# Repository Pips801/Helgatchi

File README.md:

this is an awesome project by 801labs.  calling it "by-sysaaron" was kind of stupid, sorry; i've been hacking around on it with ai.  at this time, i've added:
- a menu that lets you display any of Helga's animations
- a menu that lets you change the LED mode
- a menu that lets you trigger party mode
- a "continuous vibes" mode (NOTE: only use with flared base antenna)

# Helgatchi
Handheld BLE + WiFi Hunter

## What is it?
A portable, hand-held BLE beacon and WiFi AP scanner/hunter, with built-in alerting, 1.69” full-color screen, and external SMA-RP antenna all powered by the XIAO ESP32-S3. 

The Helgatchi will passively scan for BLE devices and WiFi SSIDs/APs, and alert when specific Manufacturers, naming schemes, or services are discovered. 

It can be configured to alert anything you want, such as:
- ALPR/Surveilance equipment
- Tactical equipment
- Cameras
- Hidden cameras
- Fitness wearables
- Audio/Video devices

You can create rules based on the following fields
|   🐑  	| MAC address 	| OUI (explicit) 	| OUI organization 	| MFG (explicit) 	| MFG organization 	| 802.11 SIG 	| Device name 	| SSID 	|
|------	|-------------	|----------------	|------------------	|----------------	|------------------	|------------	|-------------	|------	|
| WiFi 	|      ✅      	|        ✅       	|         ✅        	|        ❌       	|         ❌        	|      ✅     	|      ❌      	|   ✅  	|
| BLE  	|      ✅      	|        ✅       	|         ✅        	|        ✅       	|         ✅        	|      ❌     	|      ✅      	|   ❌  	|

## Key Features
- Enclosed, portable, battery powered handheld rechargeable BLE and WiFi scanner and hunter that can live in your pocket.
- Passively scans for beacons in the background in-between sleeping - maximizing battery life. You can configure 
- Powered by the XIAO ESP32-S3
- 6 RGB LEDs
- 1.69" rounded screen
- Vibration motor for alerts
- You can change
  - Color scheme
  - Alert settings
    - Vibrate
    - LEDs
    - Screen Wake
  - Scan settings
    - Sleep duration
    - Scan duration
  - Rules for alerts
    - MAC address (BLE, WiFi)
    - Manufacturer (BLE, WiFi OUI)
    - Device name (BLE name, WiFi SSID)
    - Service (BLE)

## Specifications

| Spec      | Info                                             	|
|----------	|---------------------------------------------------	|
| MCU      	| XIAO ESP32-S3                                     	|
| Flash    	| 8MB                                               	|
| Battery  	| 400mAh - 1200mAh 3.7v LiPo                        	|
| Screen   	| Waveshare 1.69” LCD - 240p × 280p                 	|
| Antenna  	| XIAO -> u.FL > back PCB > SMA-RP > 2.4Ghz antenna 	|
| Size     	| Width: 50mm Length: 80mm              	|

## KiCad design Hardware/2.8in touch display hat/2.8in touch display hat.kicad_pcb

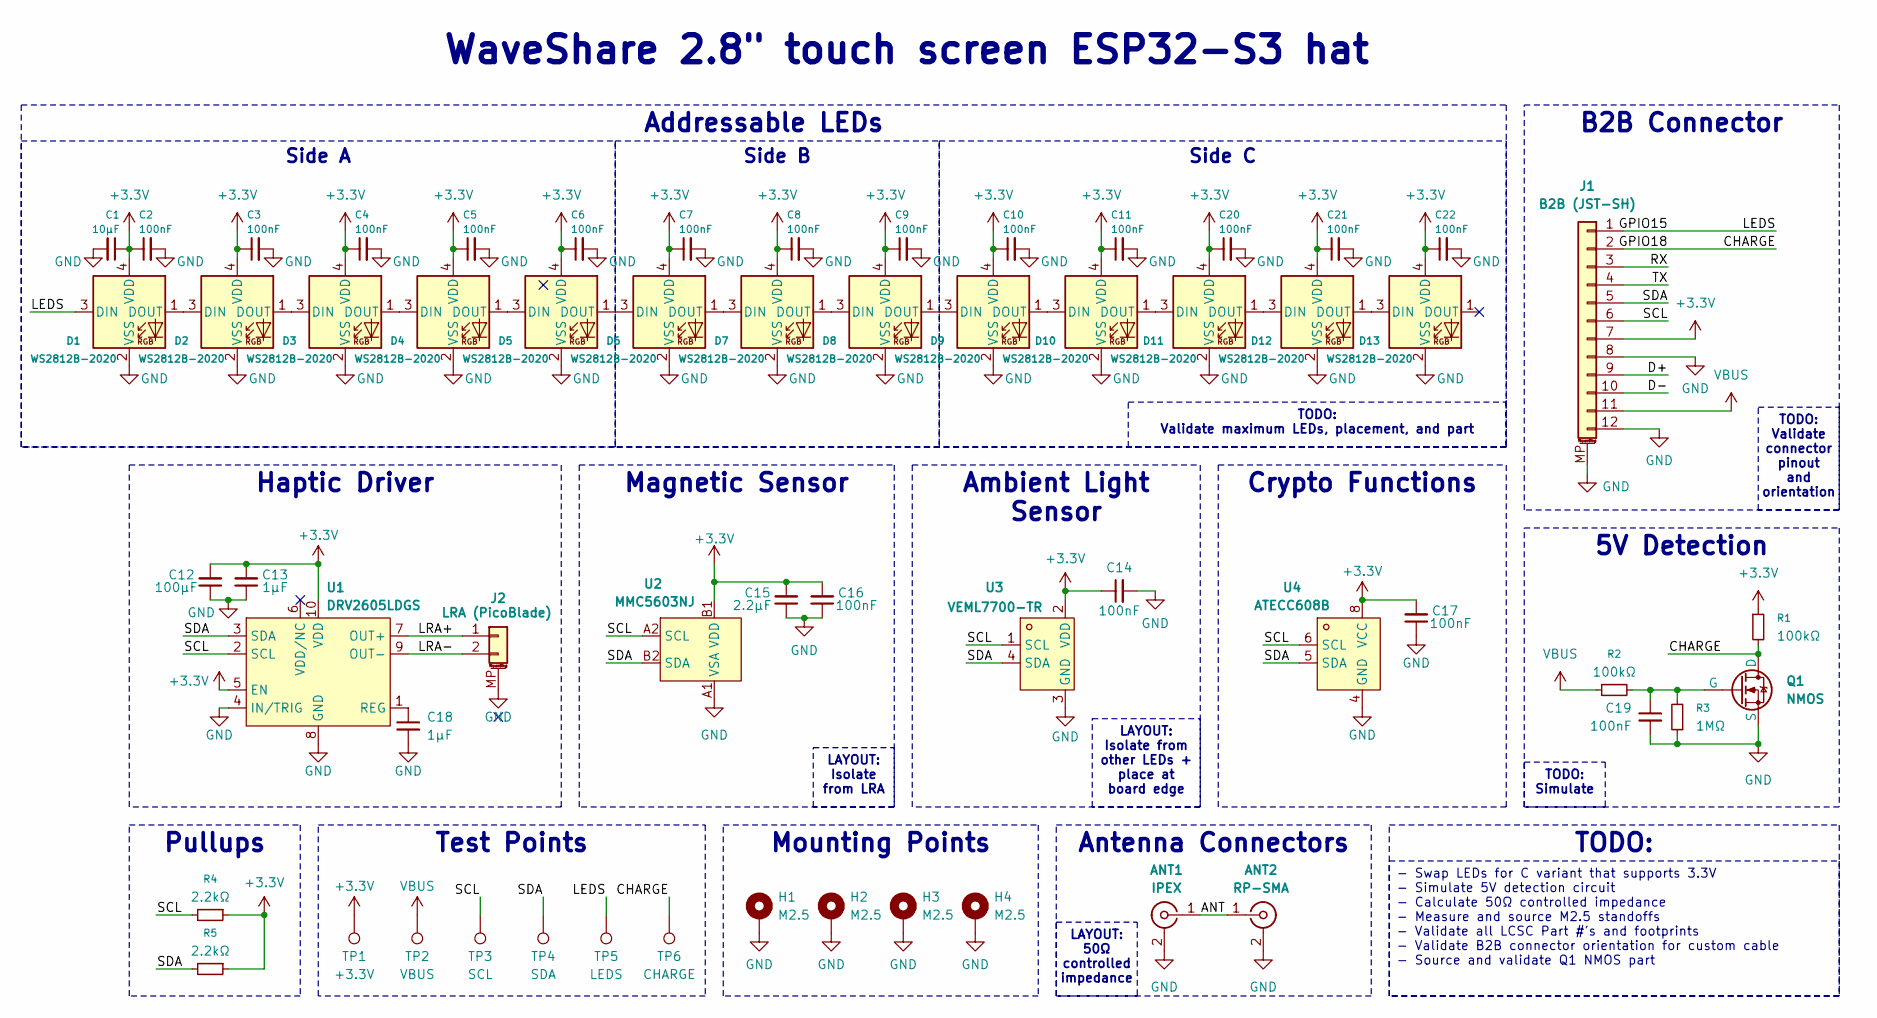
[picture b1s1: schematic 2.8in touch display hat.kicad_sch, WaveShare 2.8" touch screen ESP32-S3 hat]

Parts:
ANT1: IPEX; U.FL_Molex_MCRF_73412-0110_Vertical
ANT2: RP-SMA; SMA_Amphenol_901-143_Horizontal
C1: 10μF; C_1206_3216Metric
C2, C3, C4, C5, C6, C7, C8, C9, C10, C11, C14, C16, C17, C19, C20, C21, C22: 100nF; C_0603_1608Metric
C12: 100μF; C_0603_1608Metric
C13, C18: 1μF; C_0603_1608Metric
C15: 2.2μF; C_0603_1608Metric
D1, D2, D3, D4, D5, D6, D7, D8, D9, D10, D11, D12, D13: WS2812B-2020; LED_WS2812B-2020_PLCC4_2.0x2.0mm
H1, H2, H3, H4: M2.5; Mounting_Wuerth_WA-SMSI-M2.5_H1.5mm_9774015151
J1: B2B (JST-SH); JST_SH_SM12B-SRSS-TB_1x12-1MP_P1.00mm_Horizontal
J2: LRA (PicoBlade); Molex_PicoBlade_53261-0271_1x02-1MP_P1.25mm_Horizontal
Q1: NMOS; SOT-23-3
R1, R2: 100kΩ; R_0603_1608Metric
R3: 1MΩ; R_0603_1608Metric
R4, R5: 2.2kΩ; R_0603_1608Metric
TP1: +3.3V; TestPoint_Pad_D1.0mm
TP2: VBUS; TestPoint_Pad_D1.0mm
TP3: SCL; TestPoint_Pad_D1.0mm
TP4: SDA; TestPoint_Pad_D1.0mm
TP5: LEDS; TestPoint_Pad_D1.0mm
TP6: CHARGE; TestPoint_Pad_D1.0mm
U1: DRV2605LDGS; TSSOP-10_3x3mm_P0.5mm; LCSC Part # C504893
U2: MMC5603NJ; FLIPCHIP-4_L0.8-W0.8-R2-C2-P0.40-TL; MPN MMC5603NJ; LCSC Part C404328
U3: VEML7700-TR; LED-SMD_4P-L6.8-W2.4_VEML7700-TR; MPN VEML7700-TR; LCSC Part C504893
U4: ATECC608B; SOIC-8-1EP_3.9x4.9mm_P1.27mm_EP2.29x3mm; MPN ATECC608B-SSHDA-T; LCSC Part C1518769

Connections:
+3.3V: C1.1, C2.1, C3.1, C4.1, C5.1, C6.1, C7.1, C8.1, C9.1, C10.1, C11.1, C12.2, C13.2, C14.1, C15.2, C16.2, C17.2, C20.1, C21.1, C22.1, D1.4 (VDD), D2.4 (VDD), D3.4 (VDD), D4.4 (VDD), D5.4 (VDD), D6.4 (VDD), D7.4 (VDD), D8.4 (VDD), D9.4 (VDD), D10.4 (VDD), D11.4 (VDD), D12.4 (VDD), D13.4 (VDD), J1.7, R1.1, R4.1, R5.1, TP1.1 (1_1), U1.5 (EN), U1.10 (VDD), U2.B1 (VDD), U3.2 (VDD), U4.8 (VCC)
/ANT: ANT1.1 (In), ANT2.1 (In)
/CHARGE: J1.2, Q1.1 (D), R1.2, TP6.1 (1_1)
/D+: J1.9
/D-: J1.10
/GPIO15: D1.3 (DIN), J1.1, TP5.1 (1_1)
/LRA+: J2.1, U1.7 (OUT+)
/LRA-: J2.2, U1.9 (OUT-)
/RX: J1.3
/SCL: J1.6, R4.2, TP3.1 (1_1), U1.2 (SCL), U2.A2 (SCL), U3.1 (SCL), U4.6 (SCL)
/SDA: J1.5, R5.2, TP4.1 (1_1), U1.3 (SDA), U2.B2 (SDA), U3.4 (SDA), U4.5 (SDA)
/TX: J1.4
GND: ANT1.2 (Ext), ANT2.2 (Ext), C1.2, C2.2, C3.2, C4.2, C5.2, C6.2, C7.2, C8.2, C9.2, C10.2, C11.2, C12.1, C13.1, C14.2, C15.1, C16.1, C17.1, C18.2, C19.2, C20.2, C21.2, C22.2, D1.2 (VSS), D2.2 (VSS), D3.2 (VSS), D4.2 (VSS), D5.2 (VSS), D6.2 (VSS), D7.2 (VSS), D8.2 (VSS), D9.2 (VSS), D10.2 (VSS), D11.2 (VSS), D12.2 (VSS), D13.2 (VSS), H1.1 (1_1), H2.1 (1_1), H3.1 (1_1), H4.1 (1_1), J1.8, J1.12, J1.MP (MountPin), J2.MP (MountPin), Q1.3 (S), R3.1, U1.4 (IN/TRIG), U1.8 (GND), U2.A1 (VSA), U3.3 (GND), U4.4 (GND)
unnamed: D1.1 (DOUT), D2.3 (DIN)
unnamed: D2.1 (DOUT), D3.3 (DIN)
unnamed: D3.1 (DOUT), D4.3 (DIN)
unnamed: D4.1 (DOUT), D5.3 (DIN)
unnamed: D5.1 (DOUT), D6.3 (DIN)
unnamed: D6.1 (DOUT), D7.3 (DIN)
unnamed: D7.1 (DOUT), D8.3 (DIN)
unnamed: D8.1 (DOUT), D9.3 (DIN)
unnamed: D9.1 (DOUT), D10.3 (DIN)
unnamed: D10.1 (DOUT), D11.3 (DIN)
unnamed: D11.1 (DOUT), D12.3 (DIN)
unnamed: D12.1 (DOUT), D13.3 (DIN)
unnamed: C19.1, Q1.2 (G), R2.2, R3.2
unnamed: C18.1, U1.1 (REG)
VBUS: J1.11, R2.1, TP2.1 (1_1)

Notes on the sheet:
${TITLE}
Side B
Mounting Points
LAYOUT: Isolate from LRA
- Swap LEDs for C variant that supports 3.3V - Simulate 5V detection circuit - Calculate 50Ω controlled impedance - Measure and source M2.5 standoffs - Validate all LCSC Part #'s and footprints - Validate B2B connector orientation for custom cable - Source and validate Q1 NMOS part
Side A
Test Points
TODO: Validate maximum LEDs, placement, and part
LAYOUT: Isolate from other LEDs + place at board edge
TODO: Validate connector pinout and orientation
Magnetic Sensor
Ambient Light Sensor
Antenna Connectors
Pullups
B2B Connector
Side C
5V Detection
Addressable LEDs
LAYOUT: 50Ω controlled impedance
Crypto Functions
TODO: Simulate
TODO:
Haptic Driver

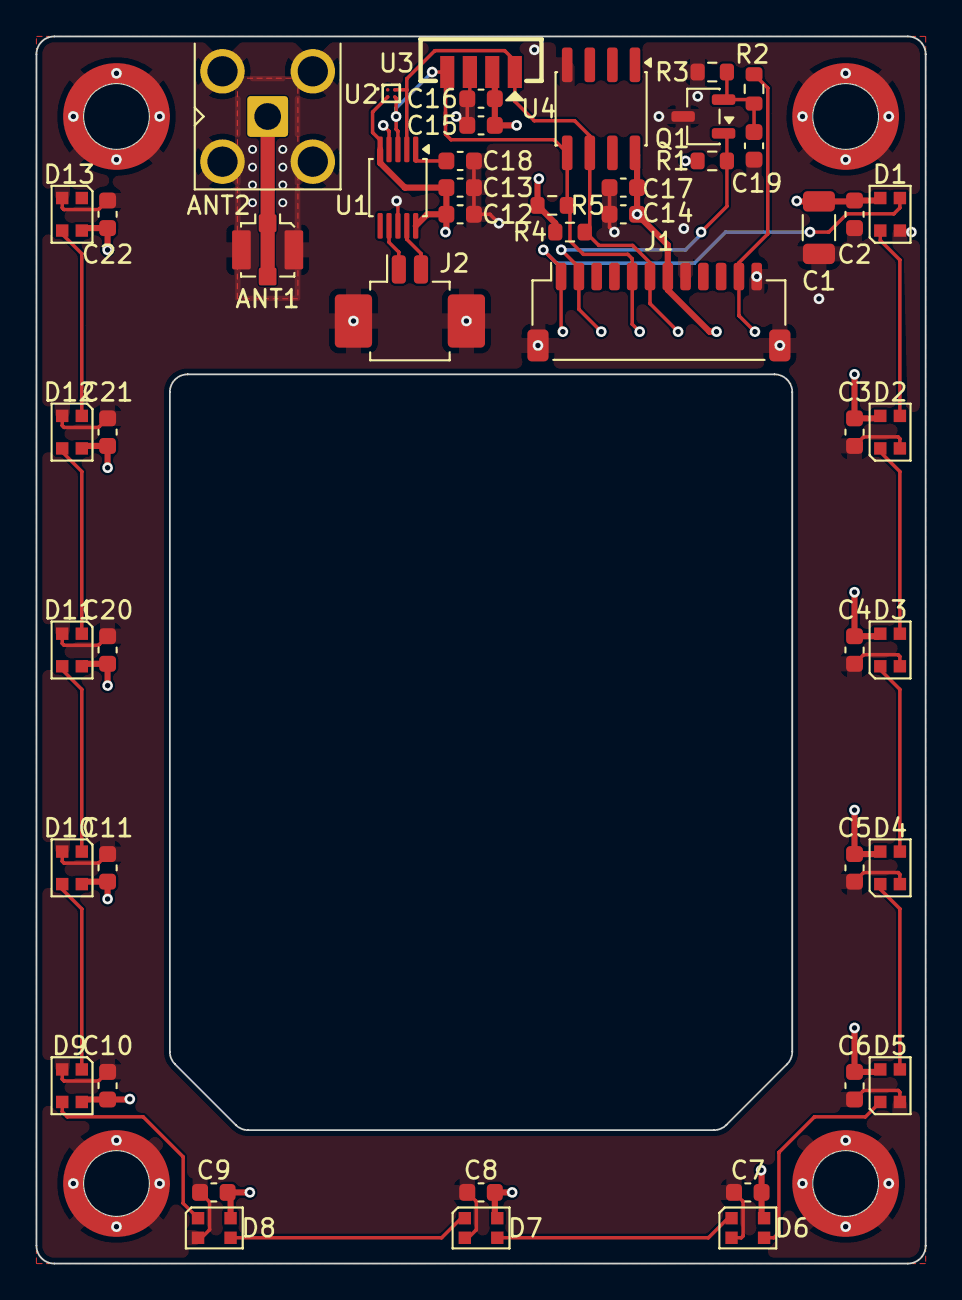
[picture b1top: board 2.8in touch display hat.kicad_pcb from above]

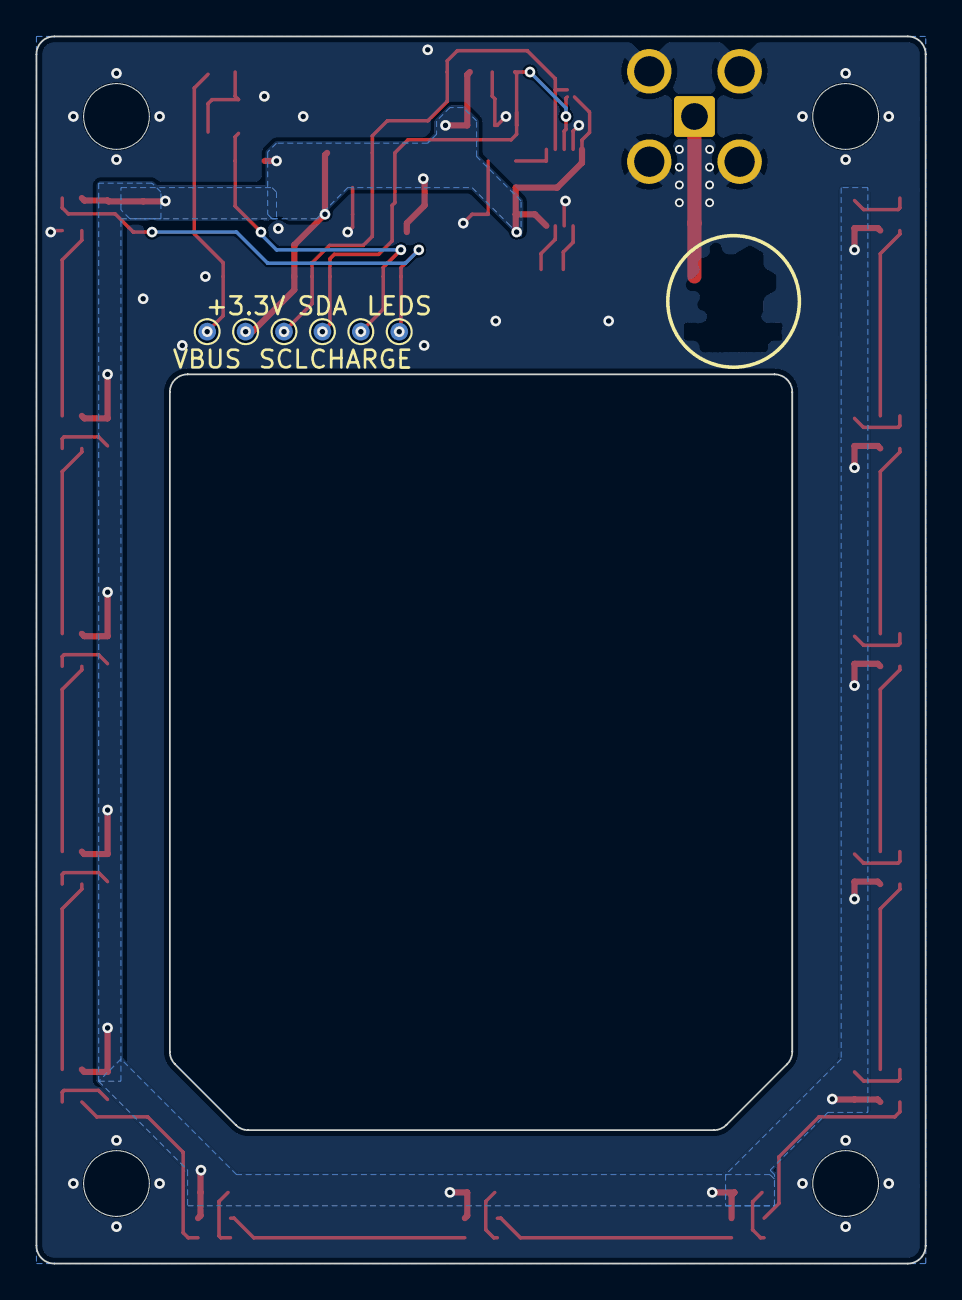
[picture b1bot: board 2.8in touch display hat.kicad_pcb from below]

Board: 2 copper layers, 50.0 x 69.0 mm, 59 parts (6 on the bottom side), 24 nets.
